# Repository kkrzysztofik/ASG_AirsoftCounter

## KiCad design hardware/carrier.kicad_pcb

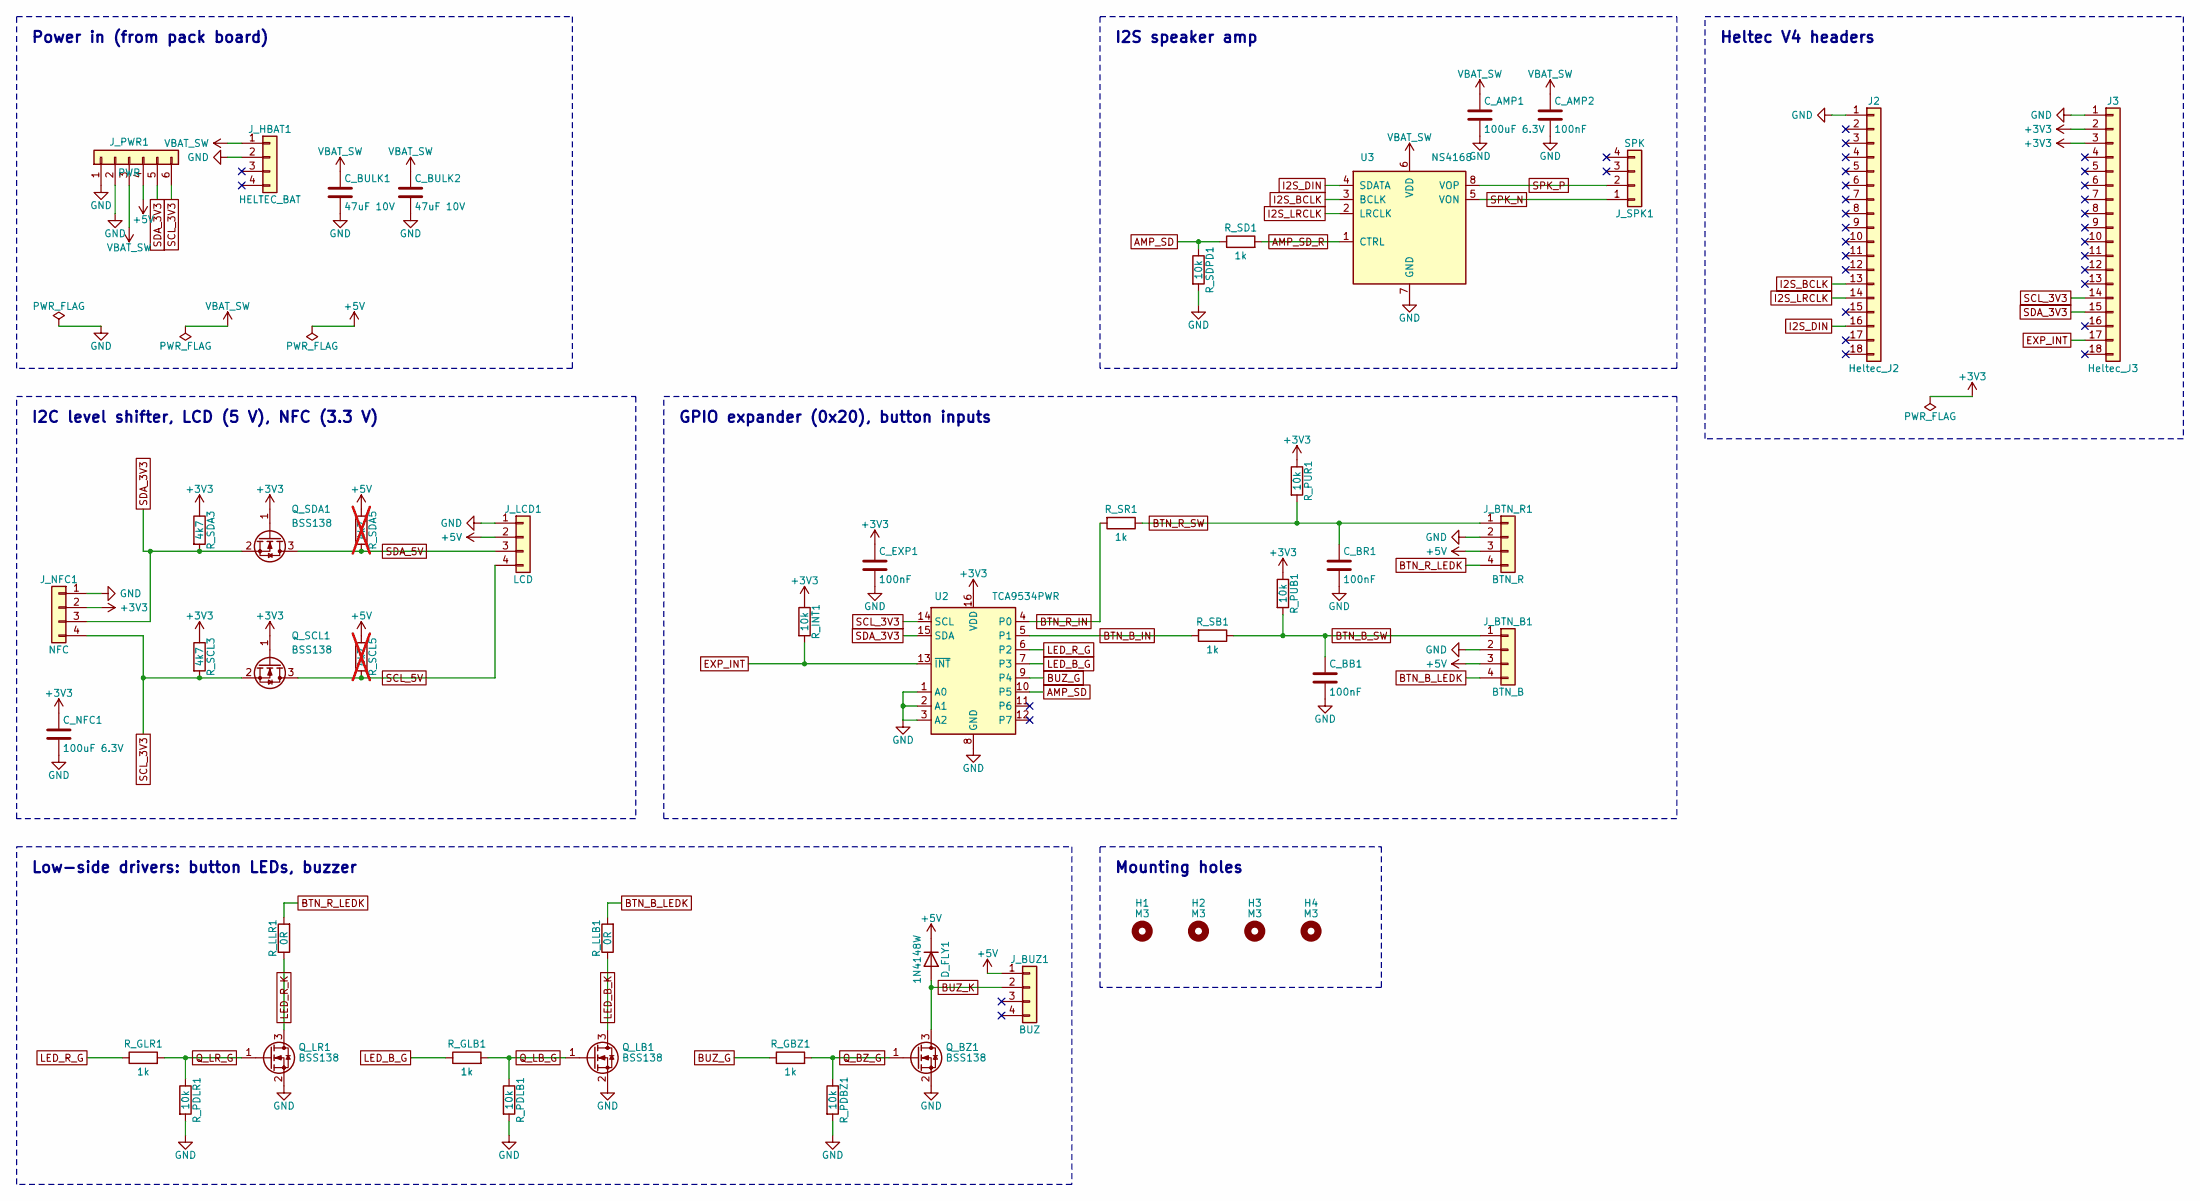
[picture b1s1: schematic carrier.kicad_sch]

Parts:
C_AMP1: 100uF 6.3V; C_1206_3216Metric_Pad1.33x1.80mm_HandSolder
C_AMP2: 100nF; C_0805_2012Metric_Pad1.18x1.45mm_HandSolder
C_BB1: 100nF; C_0805_2012Metric_Pad1.18x1.45mm_HandSolder
C_BR1: 100nF; C_0805_2012Metric_Pad1.18x1.45mm_HandSolder
C_BULK1, C_BULK2: 47uF 10V; C_1206_3216Metric_Pad1.33x1.80mm_HandSolder
C_EXP1: 100nF; C_0805_2012Metric_Pad1.18x1.45mm_HandSolder
C_NFC1: 100uF 6.3V; C_1206_3216Metric_Pad1.33x1.80mm_HandSolder
D_FLY1: 1N4148W; D_SOD-123
H1, H2, H3, H4: M3; MountingHole_3.2mm_M3
J2: Heltec_J2; PinSocket_1x18_P2.54mm_Vertical
J3: Heltec_J3; PinSocket_1x18_P2.54mm_Vertical
J_BTN_B1: BTN_B; JST_XH_B4B-XH-A_1x04_P2.50mm_Vertical
J_BTN_R1: BTN_R; JST_XH_B4B-XH-A_1x04_P2.50mm_Vertical
J_BUZ1: BUZ; JST_XH_B4B-XH-A_1x04_P2.50mm_Vertical
J_HBAT1: HELTEC_BAT; JST_XH_B4B-XH-A_1x04_P2.50mm_Vertical
J_LCD1: LCD; JST_XH_B4B-XH-A_1x04_P2.50mm_Vertical
J_NFC1: NFC; JST_XH_B4B-XH-A_1x04_P2.50mm_Vertical
J_PWR1: PWR; JST_XH_B6B-XH-A_1x06_P2.50mm_Vertical
J_SPK1: SPK; JST_XH_B4B-XH-A_1x04_P2.50mm_Vertical
Q_BZ1: BSS138; SOT-23
Q_LB1: BSS138; SOT-23
Q_LR1: BSS138; SOT-23
Q_SCL1: BSS138; SOT-23
Q_SDA1: BSS138; SOT-23
R_GBZ1: 1k; R_0805_2012Metric_Pad1.20x1.40mm_HandSolder
R_GLB1: 1k; R_0805_2012Metric_Pad1.20x1.40mm_HandSolder
R_GLR1: 1k; R_0805_2012Metric_Pad1.20x1.40mm_HandSolder
R_INT1: 10k; R_0805_2012Metric_Pad1.20x1.40mm_HandSolder
R_LLB1: 0R; R_0805_2012Metric_Pad1.20x1.40mm_HandSolder
R_LLR1: 0R; R_0805_2012Metric_Pad1.20x1.40mm_HandSolder
R_PDBZ1: 10k; R_0805_2012Metric_Pad1.20x1.40mm_HandSolder
R_PDLB1: 10k; R_0805_2012Metric_Pad1.20x1.40mm_HandSolder
R_PDLR1: 10k; R_0805_2012Metric_Pad1.20x1.40mm_HandSolder
R_PUB1: 10k; R_0805_2012Metric_Pad1.20x1.40mm_HandSolder
R_PUR1: 10k; R_0805_2012Metric_Pad1.20x1.40mm_HandSolder
R_SB1: 1k; R_0805_2012Metric_Pad1.20x1.40mm_HandSolder
R_SCL3: 4k7; R_0805_2012Metric_Pad1.20x1.40mm_HandSolder
R_SCL5: 4k7; R_0805_2012Metric_Pad1.20x1.40mm_HandSolder; not fitted
R_SD1: 1k; R_0805_2012Metric_Pad1.20x1.40mm_HandSolder
R_SDA3: 4k7; R_0805_2012Metric_Pad1.20x1.40mm_HandSolder
R_SDA5: 4k7; R_0805_2012Metric_Pad1.20x1.40mm_HandSolder; not fitted
R_SDPD1: 10k; R_0805_2012Metric_Pad1.20x1.40mm_HandSolder
R_SR1: 1k; R_0805_2012Metric_Pad1.20x1.40mm_HandSolder
U2: TCA9534PWR; TSSOP-16_4.4x5mm_P0.65mm
U3: NS4168; HSOP-8-1EP_3.9x4.9mm_P1.27mm_EP2.3x2.3mm_ThermalVias

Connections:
+3V3: C_EXP1.1, C_NFC1.1, J3.2, J3.3, J_NFC1.2, Q_SCL1.1 (G), Q_SDA1.1 (G), R_INT1.1, R_PUB1.1, R_PUR1.1, R_SCL3.1, R_SDA3.1, U2.16 (VDD)
+5V: D_FLY1.1 (K), J_BTN_B1.3, J_BTN_R1.3, J_BUZ1.1, J_LCD1.2, J_PWR1.4, R_SCL5.1, R_SDA5.1
AMP_SD: R_SD1.1, R_SDPD1.1, U2.10 (P5)
AMP_SD_R: R_SD1.2, U3.1 (CTRL)
BTN_B_IN: R_SB1.2, U2.5 (P1)
BTN_B_LEDK: J_BTN_B1.4, R_LLB1.2
BTN_B_SW: C_BB1.1, J_BTN_B1.1, R_PUB1.2, R_SB1.1
BTN_R_IN: R_SR1.2, U2.4 (P0)
BTN_R_LEDK: J_BTN_R1.4, R_LLR1.2
BTN_R_SW: C_BR1.1, J_BTN_R1.1, R_PUR1.2, R_SR1.1
BUZ_G: R_GBZ1.1, U2.9 (P4)
BUZ_K: D_FLY1.2 (A), J_BUZ1.2, Q_BZ1.3 (D)
EXP_INT: J3.17, R_INT1.2, U2.13 (~INT)
GND: C_AMP1.2, C_AMP2.2, C_BB1.2, C_BR1.2, C_BULK1.2, C_BULK2.2, C_EXP1.2, C_NFC1.2, J2.1, J3.1, J_BTN_B1.2, J_BTN_R1.2, J_HBAT1.2, J_LCD1.1, J_NFC1.1, J_PWR1.1, J_PWR1.2, Q_BZ1.2 (S), Q_LB1.2 (S), Q_LR1.2 (S), R_PDBZ1.2, R_PDLB1.2, R_PDLR1.2, R_SDPD1.2, U2.1 (A0), U2.2 (A1), U2.3 (A2), U2.8 (GND), U3.7 (GND), U3.9 (EP)
I2S_BCLK: J2.13, U3.3 (BCLK)
I2S_DIN: J2.16, U3.4 (SDATA)
I2S_LRCLK: J2.14, U3.2 (LRCLK)
LED_B_G: R_GLB1.1, U2.7 (P3)
LED_B_K: Q_LB1.3 (D), R_LLB1.1
LED_R_G: R_GLR1.1, U2.6 (P2)
LED_R_K: Q_LR1.3 (D), R_LLR1.1
Q_BZ_G: Q_BZ1.1 (G), R_GBZ1.2, R_PDBZ1.1
Q_LB_G: Q_LB1.1 (G), R_GLB1.2, R_PDLB1.1
Q_LR_G: Q_LR1.1 (G), R_GLR1.2, R_PDLR1.1
SCL_3V3: J3.14, J_NFC1.4, J_PWR1.6, Q_SCL1.2 (S), R_SCL3.2, U2.14 (SCL)
SCL_5V: J_LCD1.4, Q_SCL1.3 (D), R_SCL5.2
SDA_3V3: J3.15, J_NFC1.3, J_PWR1.5, Q_SDA1.2 (S), R_SDA3.2, U2.15 (SDA)
SDA_5V: J_LCD1.3, Q_SDA1.3 (D), R_SDA5.2
SPK_N: J_SPK1.1, U3.5 (VON)
SPK_P: J_SPK1.2, U3.8 (VOP)
VBAT_SW: C_AMP1.1, C_AMP2.1, C_BULK1.1, C_BULK2.1, J_HBAT1.1, J_PWR1.3, U3.6 (VDD)

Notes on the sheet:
Power in (from pack board)
I2S speaker amp
Heltec V4 headers
I2C level shifter, LCD (5 V), NFC (3.3 V)
GPIO expander (0x20), button inputs
Low-side drivers: button LEDs, buzzer
Mounting holes

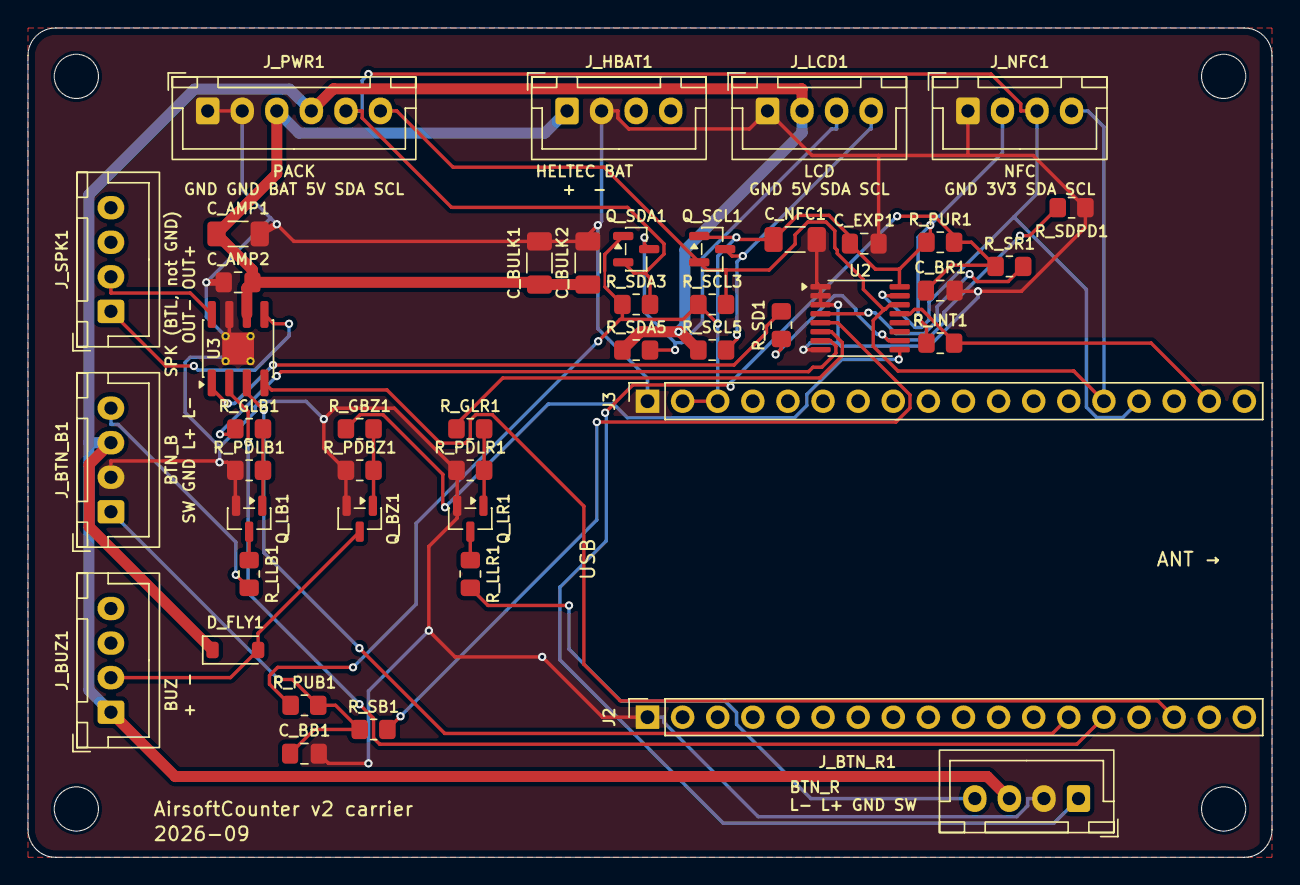
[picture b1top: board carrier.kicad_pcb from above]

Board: 2 copper layers, 90.0 x 60.0 mm, 49 parts (0 on the bottom side), 31 nets.

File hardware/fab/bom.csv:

"Refs","Value","Footprint","Qty"
"C_AMP1,C_NFC1","100uF 6.3V","Capacitor_SMD:C_1206_3216Metric_Pad1.33x1.80mm_HandSolder","2"
"C_AMP2,C_BB1,C_BR1,C_EXP1","100nF","Capacitor_SMD:C_0805_2012Metric_Pad1.18x1.45mm_HandSolder","4"
"C_BULK1,C_BULK2","47uF 10V","Capacitor_SMD:C_1206_3216Metric_Pad1.33x1.80mm_HandSolder","2"
"D_FLY1","1N4148W","Diode_SMD:D_SOD-123","1"
"J2","Heltec_J2","Connector_PinSocket_2.54mm:PinSocket_1x18_P2.54mm_Vertical","1"
"J3","Heltec_J3","Connector_PinSocket_2.54mm:PinSocket_1x18_P2.54mm_Vertical","1"
"J_BTN_B1","BTN_B","Connector_JST:JST_XH_B4B-XH-A_1x04_P2.50mm_Vertical","1"
"J_BTN_R1","BTN_R","Connector_JST:JST_XH_B4B-XH-A_1x04_P2.50mm_Vertical","1"
"J_BUZ1","BUZ","Connector_JST:JST_XH_B4B-XH-A_1x04_P2.50mm_Vertical","1"
"J_HBAT1","HELTEC_BAT","Connector_JST:JST_XH_B4B-XH-A_1x04_P2.50mm_Vertical","1"
"J_LCD1","LCD","Connector_JST:JST_XH_B4B-XH-A_1x04_P2.50mm_Vertical","1"
"J_NFC1","NFC","Connector_JST:JST_XH_B4B-XH-A_1x04_P2.50mm_Vertical","1"
"J_PWR1","PWR","Connector_JST:JST_XH_B6B-XH-A_1x06_P2.50mm_Vertical","1"
"J_SPK1","SPK","Connector_JST:JST_XH_B4B-XH-A_1x04_P2.50mm_Vertical","1"
"Q_BZ1,Q_LB1,Q_LR1,Q_SCL1,Q_SDA1","BSS138","Package_TO_SOT_SMD:SOT-23","5"
"R_GBZ1,R_GLB1,R_GLR1,R_SB1,R_SD1,R_SR1","1k","Resistor_SMD:R_0805_2012Metric_Pad1.20x1.40mm_HandSolder","6"
"R_INT1,R_PDBZ1,R_PDLB1,R_PDLR1,R_PUB1,R_PUR1,R_SDPD1","10k","Resistor_SMD:R_0805_2012Metric_Pad1.20x1.40mm_HandSolder","7"
"R_LLB1,R_LLR1","0R","Resistor_SMD:R_0805_2012Metric_Pad1.20x1.40mm_HandSolder","2"
"R_SCL3,R_SDA3","4k7","Resistor_SMD:R_0805_2012Metric_Pad1.20x1.40mm_HandSolder","2"
"U2","TCA9534PWR","Package_SO:TSSOP-16_4.4x5mm_P0.65mm","1"
"U3","NS4168","Package_SO:HSOP-8-1EP_3.9x4.9mm_P1.27mm_EP2.3x2.3mm_ThermalVias","1"

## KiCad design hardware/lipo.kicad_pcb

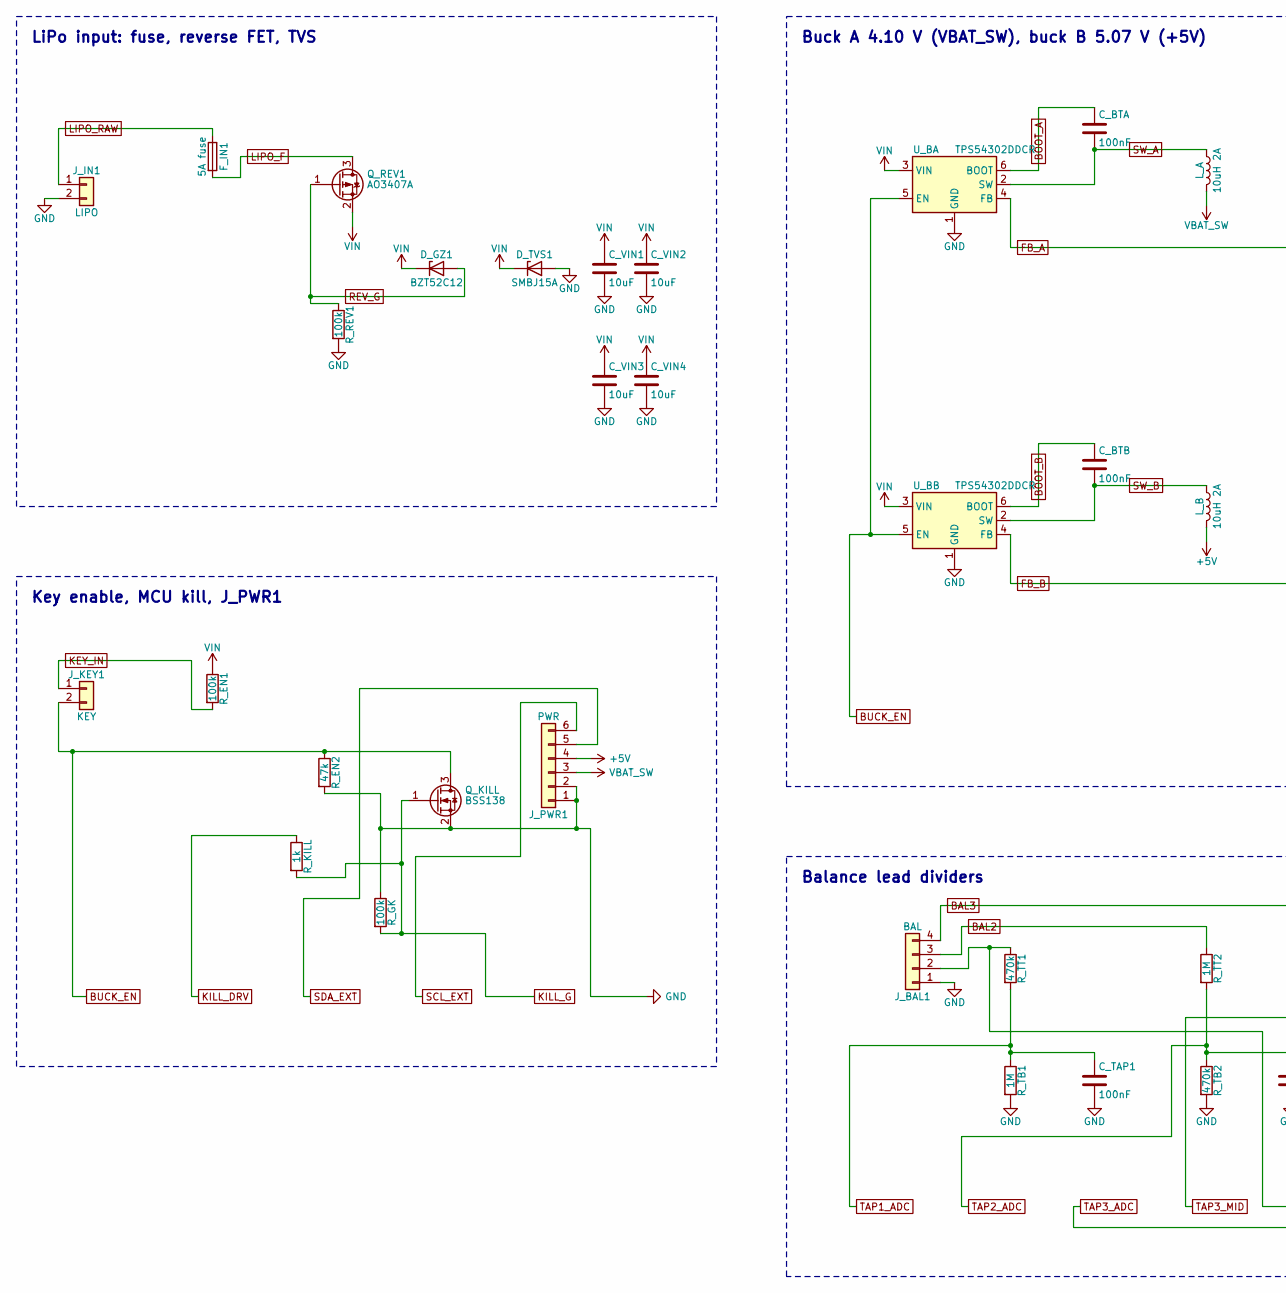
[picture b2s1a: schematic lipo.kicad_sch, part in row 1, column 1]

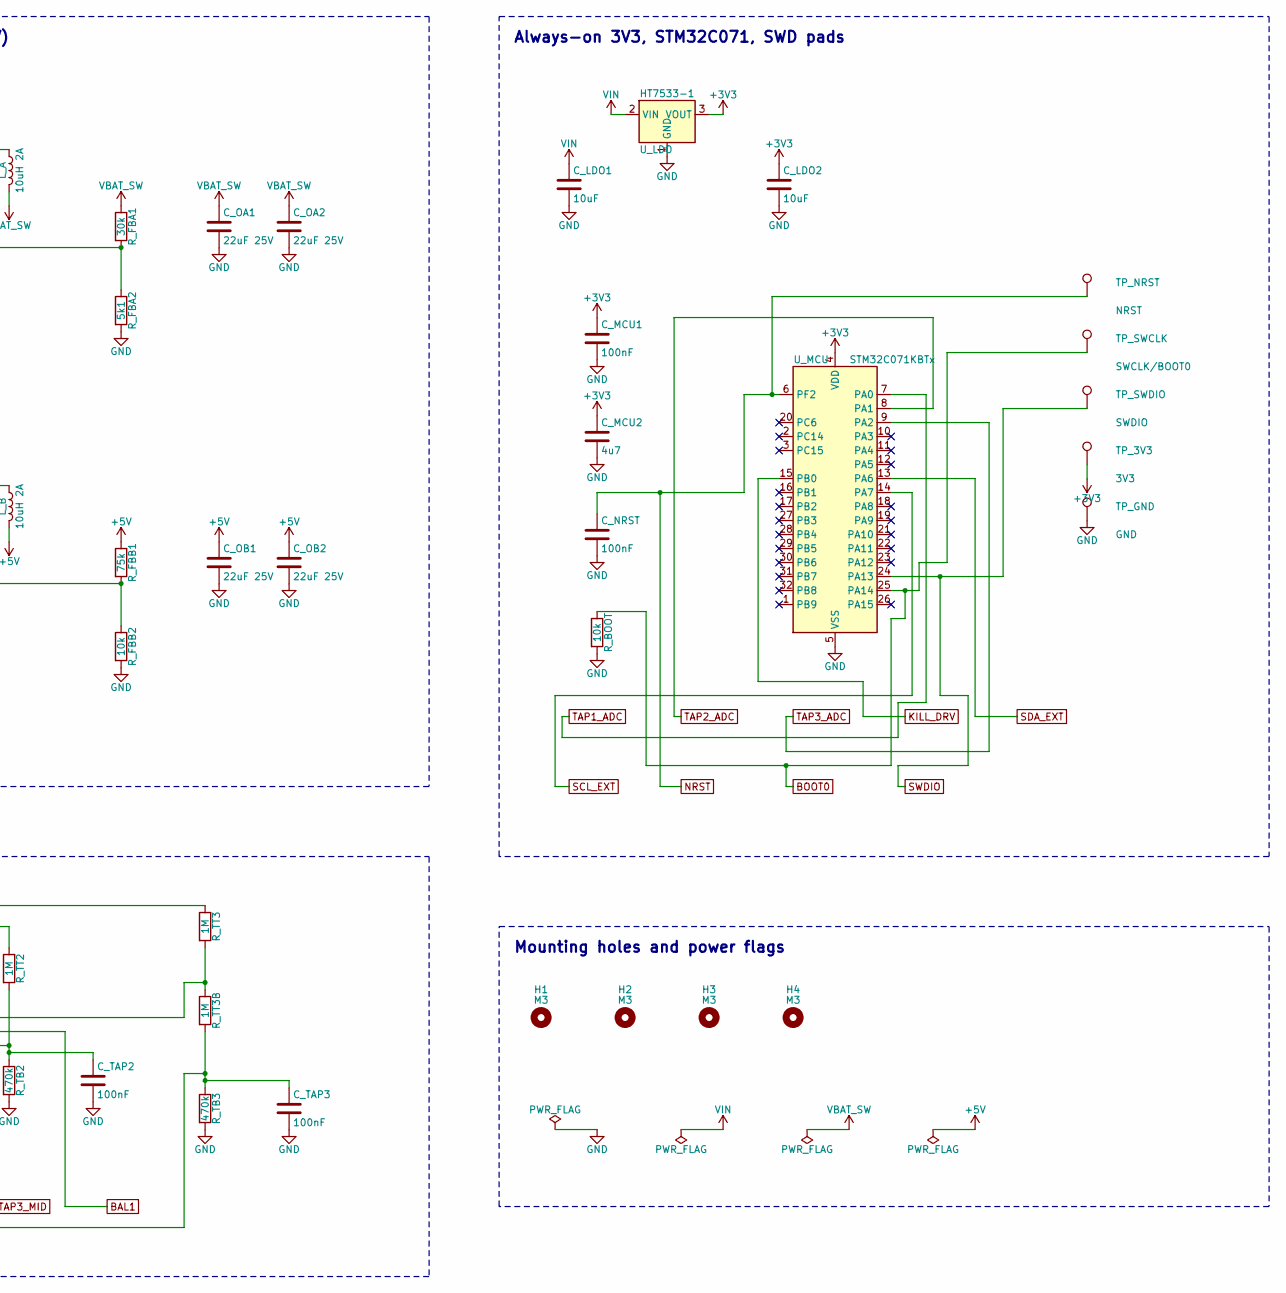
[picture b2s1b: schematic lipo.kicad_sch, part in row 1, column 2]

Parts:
C_BTA: 100nF; C_0805_2012Metric_Pad1.18x1.45mm_HandSolder
C_BTB: 100nF; C_0805_2012Metric_Pad1.18x1.45mm_HandSolder
C_LDO1, C_LDO2: 10uF; C_0805_2012Metric_Pad1.18x1.45mm_HandSolder
C_MCU1: 100nF; C_0805_2012Metric_Pad1.18x1.45mm_HandSolder
C_MCU2: 4u7; C_0805_2012Metric_Pad1.18x1.45mm_HandSolder
C_NRST: 100nF; C_0805_2012Metric_Pad1.18x1.45mm_HandSolder
C_OA1, C_OA2: 22uF 25V; C_1206_3216Metric_Pad1.33x1.80mm_HandSolder
C_OB1, C_OB2: 22uF 25V; C_1206_3216Metric_Pad1.33x1.80mm_HandSolder
C_TAP1, C_TAP2, C_TAP3: 100nF; C_0805_2012Metric_Pad1.18x1.45mm_HandSolder
C_VIN1, C_VIN2, C_VIN3, C_VIN4: 10uF; C_0805_2012Metric_Pad1.18x1.45mm_HandSolder
D_GZ1: BZT52C12; D_SOD-123
D_TVS1: SMBJ15A; D_SMB
F_IN1: 5A fuse; Fuse_1206_3216Metric_Pad1.42x1.75mm_HandSolder
H1, H2, H3, H4: M3; MountingHole_3.2mm_M3
J_BAL1: BAL; JST_XH_B4B-XH-A_1x04_P2.50mm_Vertical
J_IN1: LIPO; SolderWire-1.5sqmm_1x02_P6mm_D1.7mm_OD3mm
J_KEY1: KEY; JST_XH_B2B-XH-A_1x02_P2.50mm_Vertical
J_PWR1: PWR; JST_XH_B6B-XH-A_1x06_P2.50mm_Vertical
L_A: 10uH 2A; L_Bourns_SRN6045TA
L_B: 10uH 2A; L_Bourns_SRN6045TA
Q_KILL: BSS138; SOT-23
Q_REV1: AO3407A; SOT-23
R_BOOT: 10k; R_0805_2012Metric_Pad1.20x1.40mm_HandSolder
R_EN1: 100k; R_0805_2012Metric_Pad1.20x1.40mm_HandSolder
R_EN2: 47k; R_0805_2012Metric_Pad1.20x1.40mm_HandSolder
R_FBA1: 30k; R_0805_2012Metric_Pad1.20x1.40mm_HandSolder
R_FBA2: 5k1; R_0805_2012Metric_Pad1.20x1.40mm_HandSolder
R_FBB1: 75k; R_0805_2012Metric_Pad1.20x1.40mm_HandSolder
R_FBB2: 10k; R_0805_2012Metric_Pad1.20x1.40mm_HandSolder
R_GK: 100k; R_0805_2012Metric_Pad1.20x1.40mm_HandSolder
R_KILL: 1k; R_0805_2012Metric_Pad1.20x1.40mm_HandSolder
R_REV1: 100k; R_0805_2012Metric_Pad1.20x1.40mm_HandSolder
R_TB1: 1M; R_0805_2012Metric_Pad1.20x1.40mm_HandSolder
R_TB2, R_TB3: 470k; R_0805_2012Metric_Pad1.20x1.40mm_HandSolder
R_TT1: 470k; R_0805_2012Metric_Pad1.20x1.40mm_HandSolder
R_TT2, R_TT3, R_TT3B: 1M; R_0805_2012Metric_Pad1.20x1.40mm_HandSolder
TP_3V3: 3V3; TestPoint_Pad_D1.5mm
TP_GND: GND; TestPoint_Pad_D1.5mm
TP_NRST: NRST; TestPoint_Pad_D1.5mm
TP_SWCLK: SWCLK/BOOT0; TestPoint_Pad_D1.5mm
TP_SWDIO: SWDIO; TestPoint_Pad_D1.5mm
U_BA: TPS54302DDCR; TSOT-23-6
U_BB: TPS54302DDCR; TSOT-23-6
U_LDO: HT7533-1; SOT-89-3
U_MCU: STM32C071KBTx; LQFP-32_7x7mm_P0.8mm

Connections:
+3V3: C_LDO2.1, C_MCU1.1, C_MCU2.1, TP_3V3.1, U_LDO.3 (VOUT), U_MCU.4 (VDD)
+5V: C_OB1.1, C_OB2.1, J_PWR1.4, L_B.2, R_FBB1.1
BAL1: J_BAL1.2, R_TT1.1
BAL2: J_BAL1.3, R_TT2.1
BAL3: J_BAL1.4, R_TT3.1
BOOT0: R_BOOT.1, TP_SWCLK.1, U_MCU.25 (PA14)
BOOT_A: C_BTA.1, U_BA.6 (BOOT)
BOOT_B: C_BTB.1, U_BB.6 (BOOT)
BUCK_EN: J_KEY1.2, Q_KILL.3 (D), R_EN2.1, U_BA.5 (EN), U_BB.5 (EN)
FB_A: R_FBA1.2, R_FBA2.1, U_BA.4 (FB)
FB_B: R_FBB1.2, R_FBB2.1, U_BB.4 (FB)
GND: C_LDO1.2, C_LDO2.2, C_MCU1.2, C_MCU2.2, C_NRST.2, C_OA1.2, C_OA2.2, C_OB1.2, C_OB2.2, C_TAP1.2, C_TAP2.2, C_TAP3.2, C_VIN1.2, C_VIN2.2, C_VIN3.2, C_VIN4.2, D_TVS1.2 (A), J_BAL1.1, J_IN1.2, J_PWR1.1, J_PWR1.2, Q_KILL.2 (S), R_BOOT.2, R_EN2.2, R_FBA2.2, R_FBB2.2, R_GK.1, R_REV1.2, R_TB1.2, R_TB2.2, R_TB3.2, TP_GND.1, U_BA.1 (GND), U_BB.1 (GND), U_LDO.1 (GND), U_MCU.5 (VSS)
KEY_IN: J_KEY1.1, R_EN1.2
KILL_DRV: R_KILL.1, U_MCU.15 (PB0)
KILL_G: Q_KILL.1 (G), R_GK.2, R_KILL.2
LIPO_F: F_IN1.2, Q_REV1.3 (D)
LIPO_RAW: F_IN1.1, J_IN1.1
NRST: C_NRST.1, TP_NRST.1, U_MCU.6 (PF2)
REV_G: D_GZ1.2 (A), Q_REV1.1 (G), R_REV1.1
SCL_EXT: J_PWR1.6, U_MCU.14 (PA7)
SDA_EXT: J_PWR1.5, U_MCU.13 (PA6)
SWDIO: TP_SWDIO.1, U_MCU.24 (PA13)
SW_A: C_BTA.2, L_A.1, U_BA.2 (SW)
SW_B: C_BTB.2, L_B.1, U_BB.2 (SW)
TAP1_ADC: C_TAP1.1, R_TB1.1, R_TT1.2, U_MCU.7 (PA0)
TAP2_ADC: C_TAP2.1, R_TB2.1, R_TT2.2, U_MCU.8 (PA1)
TAP3_ADC: C_TAP3.1, R_TB3.1, R_TT3B.2, U_MCU.9 (PA2)
TAP3_MID: R_TT3.2, R_TT3B.1
VBAT_SW: C_OA1.1, C_OA2.1, J_PWR1.3, L_A.2, R_FBA1.1
VIN: C_LDO1.1, C_VIN1.1, C_VIN2.1, C_VIN3.1, C_VIN4.1, D_GZ1.1 (K), D_TVS1.1 (K), Q_REV1.2 (S), R_EN1.1, U_BA.3 (VIN), U_BB.3 (VIN), U_LDO.2 (VIN)

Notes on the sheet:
LiPo input: fuse, reverse FET, TVS
Buck A 4.10 V (VBAT_SW), buck B 5.07 V (+5V)
Key enable, MCU kill, J_PWR1
Always-on 3V3, STM32C071, SWD pads
Balance lead dividers
Mounting holes and power flags

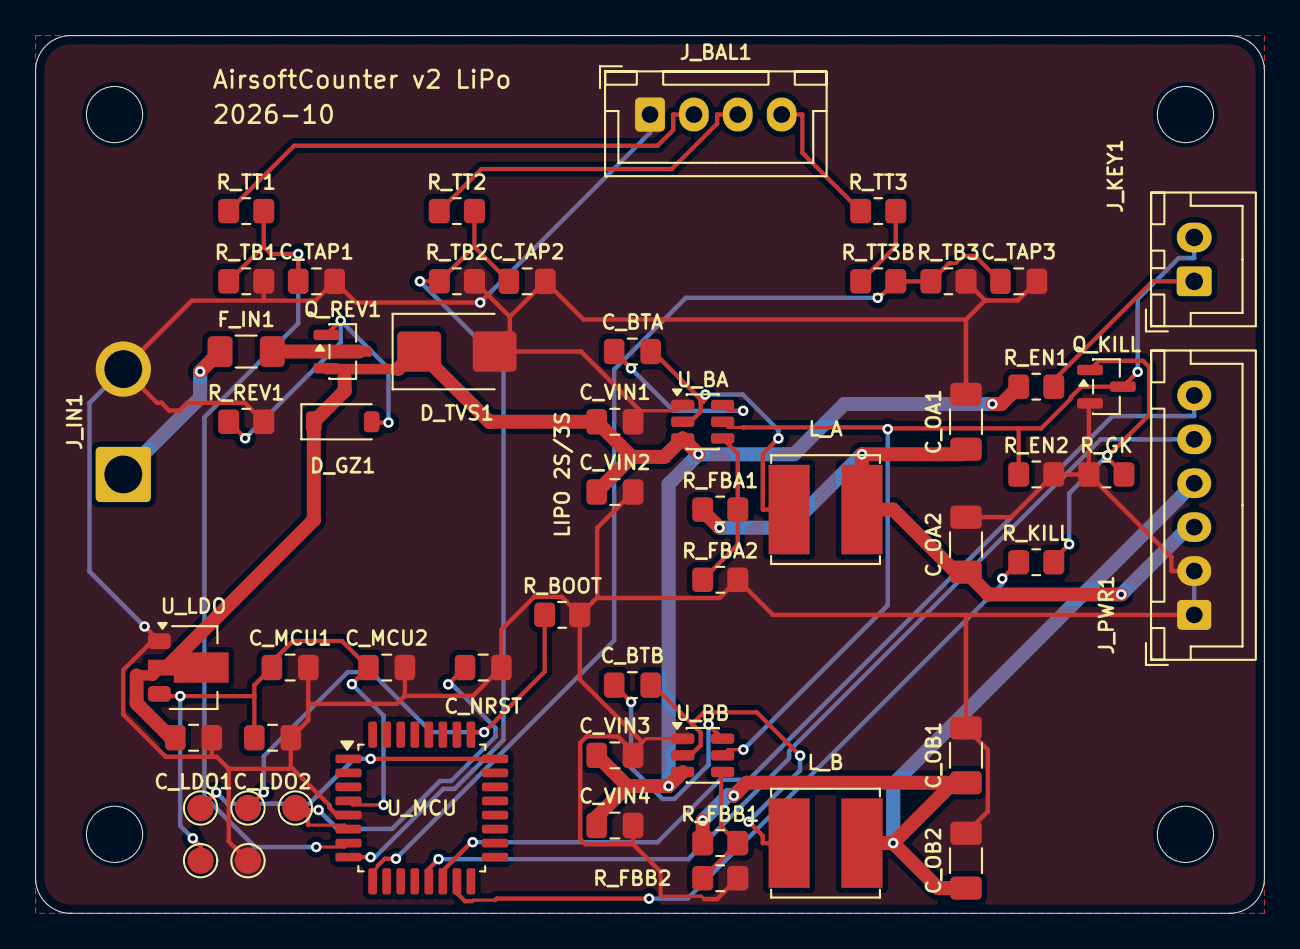
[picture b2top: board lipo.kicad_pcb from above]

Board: 2 copper layers, 70.0 x 50.0 mm, 59 parts (0 on the bottom side), 30 nets.
